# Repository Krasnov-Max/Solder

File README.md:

# Solder

Thermo controller for soldering and solder mask.

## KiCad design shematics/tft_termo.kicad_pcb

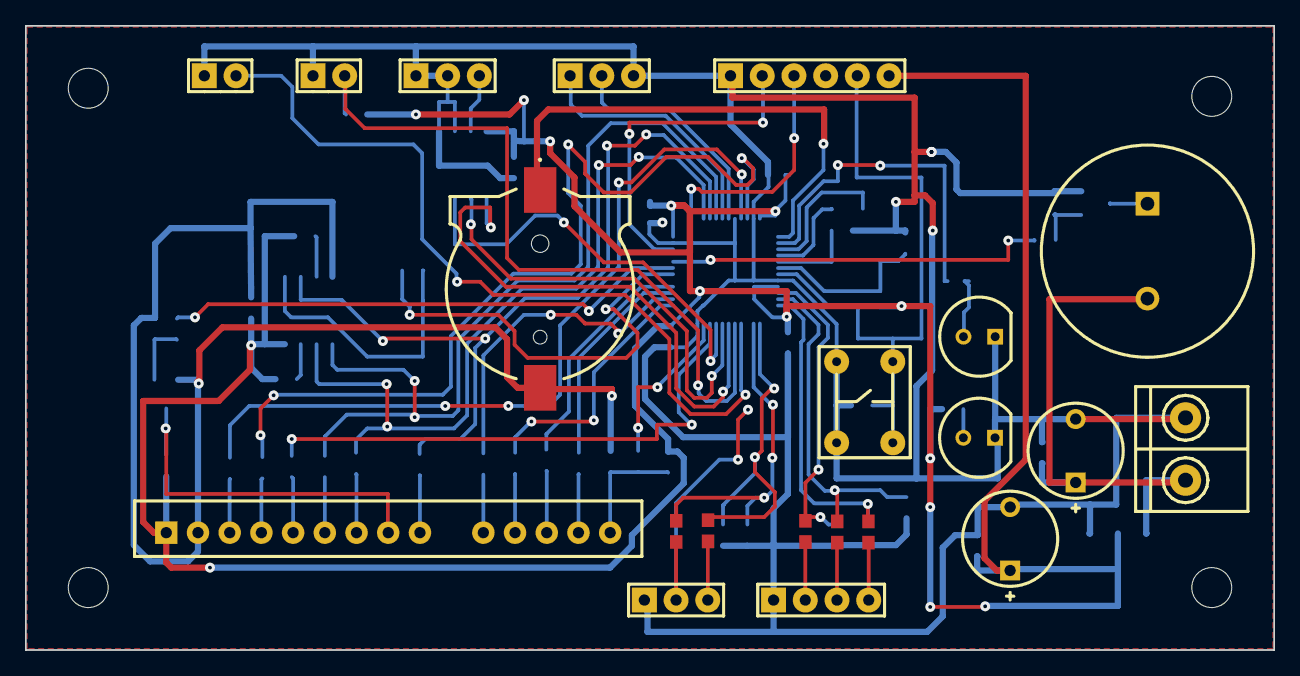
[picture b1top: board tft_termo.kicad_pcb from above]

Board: 2 copper layers, 100.0 x 50.0 mm, 74 parts (0 on the bottom side), 57 nets.

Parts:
@HOLE0, @HOLE1, @HOLE2, @HOLE3: (no value)
B1: 1056
C1, C2: 22p; CAP_0603
C3, C4, C5, C8, C9, C10, C11, C12, C13, C14, C15, C16, C17, C18: 0.1 uf; CAP_0603
C6, C7: 47 uf; CAPPR-5.08_7.62
D1, D2: LED; LED100
D3: W25Q32
HITING1: HITING; PBS_2
K1: KEY_6X6; KEY_6x6
LCD1: TFT_2.4; TFT_LCD_2_4
LS1: AST-1732MR-R; AST-01708
POWER1: POWER; 300_2_5
PROGRAM1: PROGRAM; PBS_6
Q1, Q2: BC846ALT1; SOT23
R1, R5, R6: 4K7; RES_0603
R2, R3, R4, R10, R11, R12, R13, R14, R15, R16, R17, R18, R19, R20, R21, R22, R30: 120; RES_0603
R7, R26: 47k; RES_0603
R8, R9: 330; RES_0603
R23, R24, R28, R29: 10k; RES_0603
R25, R27: 4k7; RES_0603
TERMOCOP1: TERMOCOP; PBS_3
U1: STM32F302CBT6; QFP-48_9x9x0.5
U2: MAX6675ISA; SOIC-8_150mil
U3: NCP1117; SOT-223
UART1: USART; PBS_3
XS1: PBS_4
XS2: PBS_3_15; PBS_3
Y1: 8MHz; NX5032GA
Y2: NX3215SA-32.768K
ZERRO1: ZERRO; PBS_2

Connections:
/tft_termo_1/+5V: C4.1, C6.1, LS1.2, POWER1.1, U3.3
/tft_termo_1/BACK_L: R25.1, U1.31
/tft_termo_1/BUZZER: R6.1, U1.32
/tft_termo_1/ENC_A: C14.1, R4.2, U1.10
/tft_termo_1/ENC_B: C13.1, R11.2, U1.11
/tft_termo_1/HITER: HITING1.2, U1.16
/tft_termo_1/KEY_1: C16.1, R2.2, U1.14
/tft_termo_1/KEY_2: C15.1, R12.2, U1.13
/tft_termo_1/KEY_ENC: C17.1, R10.2, U1.12
/tft_termo_1/LCD_BACKLIGHT: LCD1.8, Q2.3, R27.1
/tft_termo_1/LCD_CLK: D3.6, R16.1, U1.39
/tft_termo_1/LCD_CS: R3.1, U1.45
/tft_termo_1/LCD_DC: R14.1, U1.21
/tft_termo_1/LCD_MISO: R17.1, U1.40
/tft_termo_1/LCD_MOSI: D3.5, R15.1, U1.41
/tft_termo_1/LCD_RESET: R13.1, U1.46
/tft_termo_1/LED: R9.2, U1.2
/tft_termo_1/M_CS: R30.1, U1.30
/tft_termo_1/RX: U1.43, UART1.2
/tft_termo_1/SWCLK: PROGRAM1.3, U1.37
/tft_termo_1/SWDIO: PROGRAM1.2, U1.34
/tft_termo_1/TEMP_IN: U1.20, U2.7
/tft_termo_1/TEMP_OSC: U1.18, U2.5
/tft_termo_1/TEMP_SEL: U1.19, U2.6
/tft_termo_1/TOUCH_CS: R19.1, U1.25
/tft_termo_1/TOUCH_IRQ: R22.1, U1.22
/tft_termo_1/TOUCH_MISO: R21.1, U1.27
/tft_termo_1/TOUCH_MOSI: R20.1, U1.28
/tft_termo_1/TOUCH_SLK: R18.1, U1.26
/tft_termo_1/TX: U1.42, UART1.1
/tft_termo_1/ZERRO: R5.1, U1.17, ZERRO1.2
/tft_termo_1/nres: C3.1, K1.1, K1.2, PROGRAM1.5, R1.1, U1.7
/tft_termo_1/vbat: B1.1, U1.1
GND: B1.2, C1.2, C2.2, C3.2, C4.2, C5.2, C8.2, C9.2, C10.2, C11.2, C12.2, C13.2, C14.2, C15.2, C16.2, C17.2, C18.2, D3.4, HITING1.1, LCD1.2, POWER1.2, PROGRAM1.1, Q1.2, Q2.2, R7.1, R24.1, R26.1, TERMOCOP1.1, TERMOCOP1.2, U1.8, U1.23, U1.35, U1.44, U1.47, U2.1, U2.2, U3.1, UART1.3, XS1.1, XS2.1, ZERRO1.1
unnamed: C1.1, U1.6, Y1.2
unnamed: C2.1, U1.5, Y1.1
unnamed: D1.2, R8.1
unnamed: D2.2, R9.1
unnamed: D3.3, R29.2
unnamed: LCD1.9, R17.2
unnamed: LCD1.10, R18.2
unnamed: LCD1.11, R19.2
unnamed: LCD1.12, R20.2
unnamed: LCD1.13, R21.2
unnamed: LCD1.14, R22.2, R23.1, R24.2
unnamed: LS1.1, Q1.3
unnamed: Q1.1, R6.2, R7.2
unnamed: Q2.1, R25.2, R26.2
unnamed: R2.1, XS2.2
unnamed: R4.1, XS1.2
unnamed: R10.1, XS1.4
unnamed: R11.1, XS1.3
unnamed: R12.1, XS2.3
unnamed: TERMOCOP1.3, U2.3
unnamed: U1.3, Y2.2
unnamed: U1.4, Y2.1
VDD: C5.1, C7.1, C8.1, C9.1, C10.1, C11.1, C12.1, C18.1, PROGRAM1.6, R1.2, R5.2, R8.2, R23.2, R27.2, R28.2, R29.1, U1.9, U1.24, U1.36, U1.48, U2.4, U3.2, U3.4

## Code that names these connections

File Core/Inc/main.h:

/* USER CODE BEGIN Header */
/**
  ******************************************************************************
  * @file           : main.h
  * @brief          : Header for main.c file.
  *                   This file contains the common defines of the application.
  ******************************************************************************
  * @attention
  *
  * <h2><center>&copy; Copyright (c) 2020 STMicroelectronics.
  * All rights reserved.</center></h2>
  *
  * This software component is licensed by ST under BSD 3-Clause license,
  * the "License"; You may not use this file except in compliance with the
  * License. You may obtain a copy of the License at:
  *                        opensource.org/licenses/BSD-3-Clause
  *
  ******************************************************************************
  */
/* USER CODE END Header */

/* Define to prevent recursive inclusion -------------------------------------*/
#ifndef __MAIN_H
#define __MAIN_H

#ifdef __cplusplus
extern "C" {
#endif

/* Includes ------------------------------------------------------------------*/
#include "stm32f3xx_hal.h"

/* Private includes ----------------------------------------------------------*/
/* USER CODE BEGIN Includes */

/* USER CODE END Includes */

/* Exported types ------------------------------------------------------------*/
/* USER CODE BEGIN ET */

/* USER CODE END ET */

/* Exported constants --------------------------------------------------------*/
/* USER CODE BEGIN EC */

/* USER CODE END EC */

/* Exported macro ------------------------------------------------------------*/
/* USER CODE BEGIN EM */

/* USER CODE END EM */

/* Exported functions prototypes ---------------------------------------------*/
void Error_Handler(void);

/* USER CODE BEGIN EFP */

/* USER CODE END EFP */

/* Private defines -----------------------------------------------------------*/
#define LED_Pin GPIO_PIN_13
#define LED_GPIO_Port GPIOC
#define KEY_1_Pin GPIO_PIN_3
#define KEY_1_GPIO_Port GPIOA
#define KEY_2_Pin GPIO_PIN_4
#define KEY_2_GPIO_Port GPIOA
#define Hiter_Pin GPIO_PIN_6
#define Hiter_GPIO_Port GPIOA
#define Temperature_SCK_Pin GPIO_PIN_0
#define Temperature_SCK_GPIO_Port GPIOB
#define Temperature_CS_Pin GPIO_PIN_1
#define Temperature_CS_GPIO_Port GPIOB
#define Temperature_IN_Pin GPIO_PIN_2
#define Temperature_IN_GPIO_Port GPIOB
#define LCD_DC_Pin GPIO_PIN_10
#define LCD_DC_GPIO_Port GPIOB
#define Touch_IRQ_Pin GPIO_PIN_11
#define Touch_IRQ_GPIO_Port GPIOB
#define Touch_CS_Pin GPIO_PIN_12
#define Touch_CS_GPIO_Port GPIOB
#define Touch_SCK_Pin GPIO_PIN_13
#define Touch_SCK_GPIO_Port GPIOB
#define Touch_MISO_Pin GPIO_PIN_14
#define Touch_MISO_GPIO_Port GPIOB
#define Touch_MOSI_Pin GPIO_PIN_15
#define Touch_MOSI_GPIO_Port GPIOB
#define Memory_CS_Pin GPIO_PIN_9
#define Memory_CS_GPIO_Port GPIOA
#define BackLight_Pin GPIO_PIN_10
#define BackLight_GPIO_Port GPIOA
#define Buzzer_Pin GPIO_PIN_11
#define Buzzer_GPIO_Port GPIOA
#define LCD_CS_Pin GPIO_PIN_8
#define LCD_CS_GPIO_Port GPIOB
#define LCD_Reset_Pin GPIO_PIN_9
#define LCD_Reset_GPIO_Port GPIOB
/* USER CODE BEGIN Private defines */
#define MIN_PID 50
#define MAX_PID 900
/* USER CODE END Private defines */

#ifdef __cplusplus
}
#endif

#endif /* __MAIN_H */

/************************ (C) COPYRIGHT STMicroelectronics *****END OF FILE****/
